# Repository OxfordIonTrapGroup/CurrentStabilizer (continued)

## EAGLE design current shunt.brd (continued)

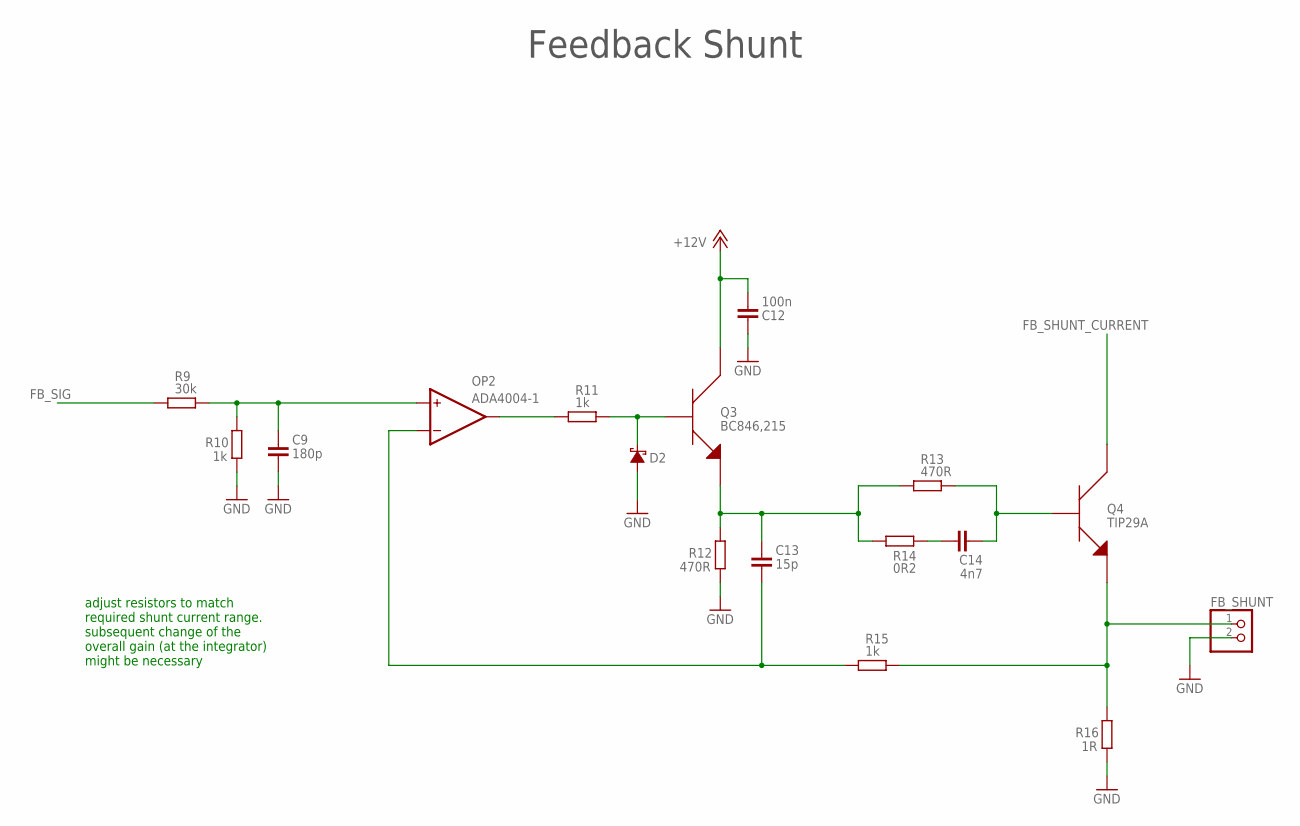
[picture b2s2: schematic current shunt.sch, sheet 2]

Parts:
C9: 180p; 0603
C12: 100n; 0603
C13: 15p; 0603
C14: 4n7; 0603
D2: DIODE_SCHOTTKY; SOD123F
FB_SHUNT: PINHD-1X2; 1X02
OP2: ADA4004-1; SOT23-5
Q3: BC846,215; SOT23
Q4: TIP29A; TO-220_DETATCHED
R9: 30k; 0603
R10, R11, R15: 1k; 0603
R12, R13: 470R; 0603
R14: 0R2; 0603
R16: 1R; 0603

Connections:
+12V: C12.1, Q3.3 (COLLECTOR); also elsewhere on the board
FB_SHUNT_CURRENT: Q4.COLLECTOR; also elsewhere on the board
FB_SIG: R9.1; also elsewhere on the board
FF_SHUNT: FB_SHUNT.1, Q4.EMITTER, R15.2, R16.2
GND: C9.2, C12.2, D2.P$2 (A), FB_SHUNT.2, R10.1, R12.1, R16.1; also elsewhere on the board
unnamed: C13.2, OP2.4 (-IN), R15.1
unnamed: C9.1, OP2.3 (+IN), R9.2, R10.2
unnamed: OP2.1 (OUT), R11.1
unnamed: D2.P$1 (K), Q3.1 (BASE), R11.2
unnamed: C13.1, Q3.2 (EMITTER), R12.2, R13.1, R14.1
unnamed: C14.2, Q4.BASE, R13.2
unnamed: C14.1, R14.2

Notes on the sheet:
Feedback Shunt
adjust resistors to match required shunt current range. subsequent change of the overall gain (at the integrator) might be necessary

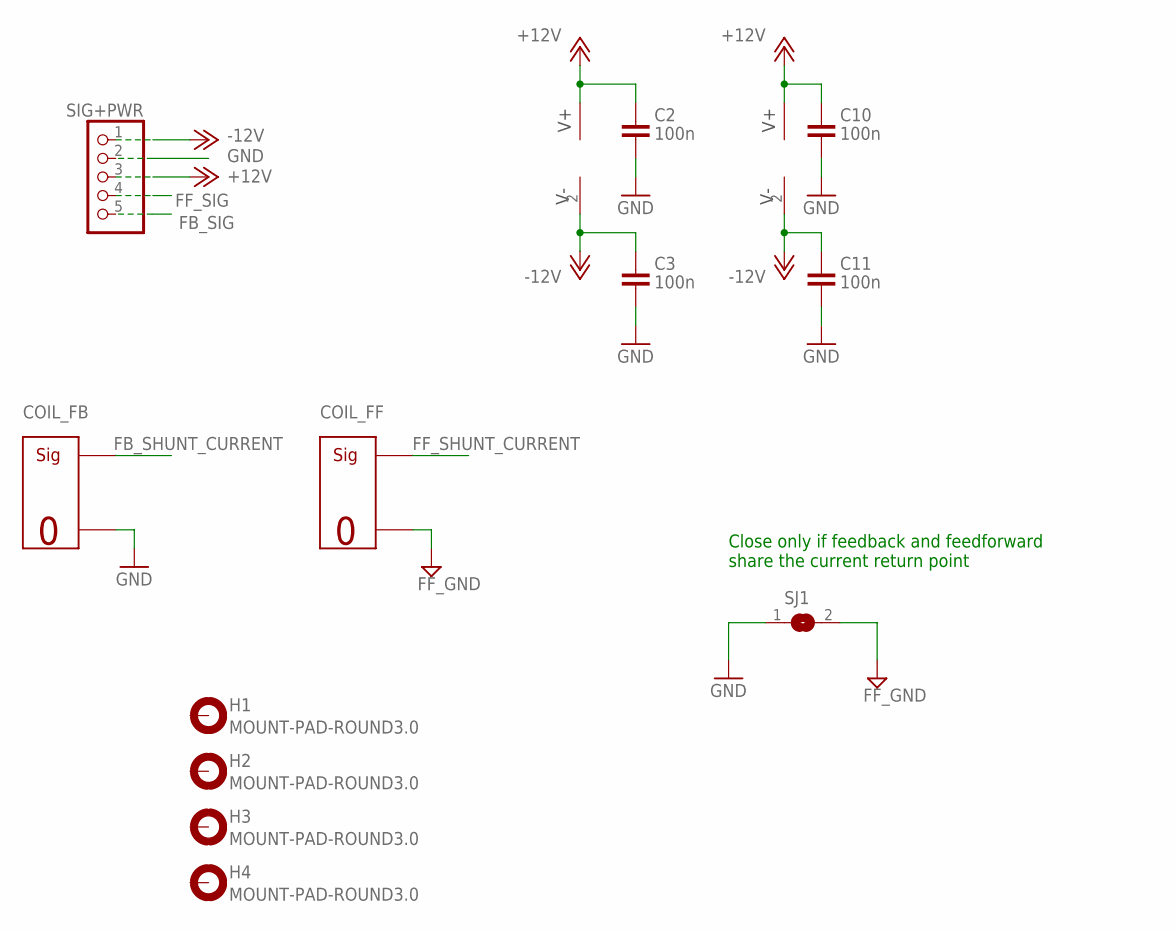
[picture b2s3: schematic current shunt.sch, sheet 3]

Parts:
C2, C3, C10, C11: 100n; 0603
COIL_FB: MOLEX_SIG_2PIN; MOLEX-2PIN
COIL_FF: MOLEX_SIG_2PIN; MOLEX-2PIN
H1, H2, H3, H4: MOUNT-PAD-ROUND3.0; 3,0-PAD
OP1, OP2: ADA4004-1; SOT23-5
SIG+PWR: MOLEX-KK-1X5; MOLEX-KK-5PIN
SJ1: SJ

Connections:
+12V: C2.1, C10.1, OP1.5 (V+), OP2.5 (V+), SIG+PWR.3; also elsewhere on the board
-12V: C3.1, C11.1, OP1.2 (V-), OP2.2 (V-), SIG+PWR.1
FB_SHUNT_CURRENT: COIL_FB.2 (SIG); also elsewhere on the board
FB_SIG: SIG+PWR.5; also elsewhere on the board
FF_GND: COIL_FF.1 (GND), SJ1.2; also elsewhere on the board
FF_SHUNT_CURRENT: COIL_FF.2 (SIG); also elsewhere on the board
FF_SIG: SIG+PWR.4; also elsewhere on the board
GND: C2.2, C3.2, C10.2, C11.2, COIL_FB.1 (GND), SIG+PWR.2, SJ1.1; also elsewhere on the board

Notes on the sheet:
Close only if feedback and feedforward share the current return point

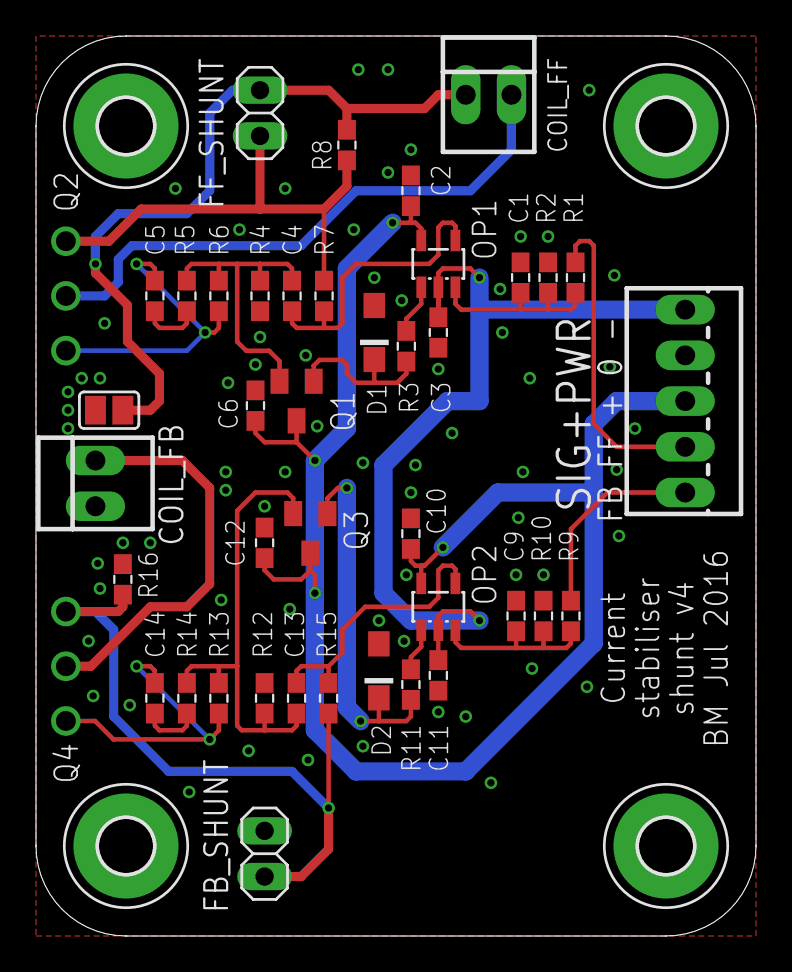
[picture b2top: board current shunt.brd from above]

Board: 2 copper layers, 40.0 x 50.0 mm, 46 parts (0 on the bottom side), 24 nets.

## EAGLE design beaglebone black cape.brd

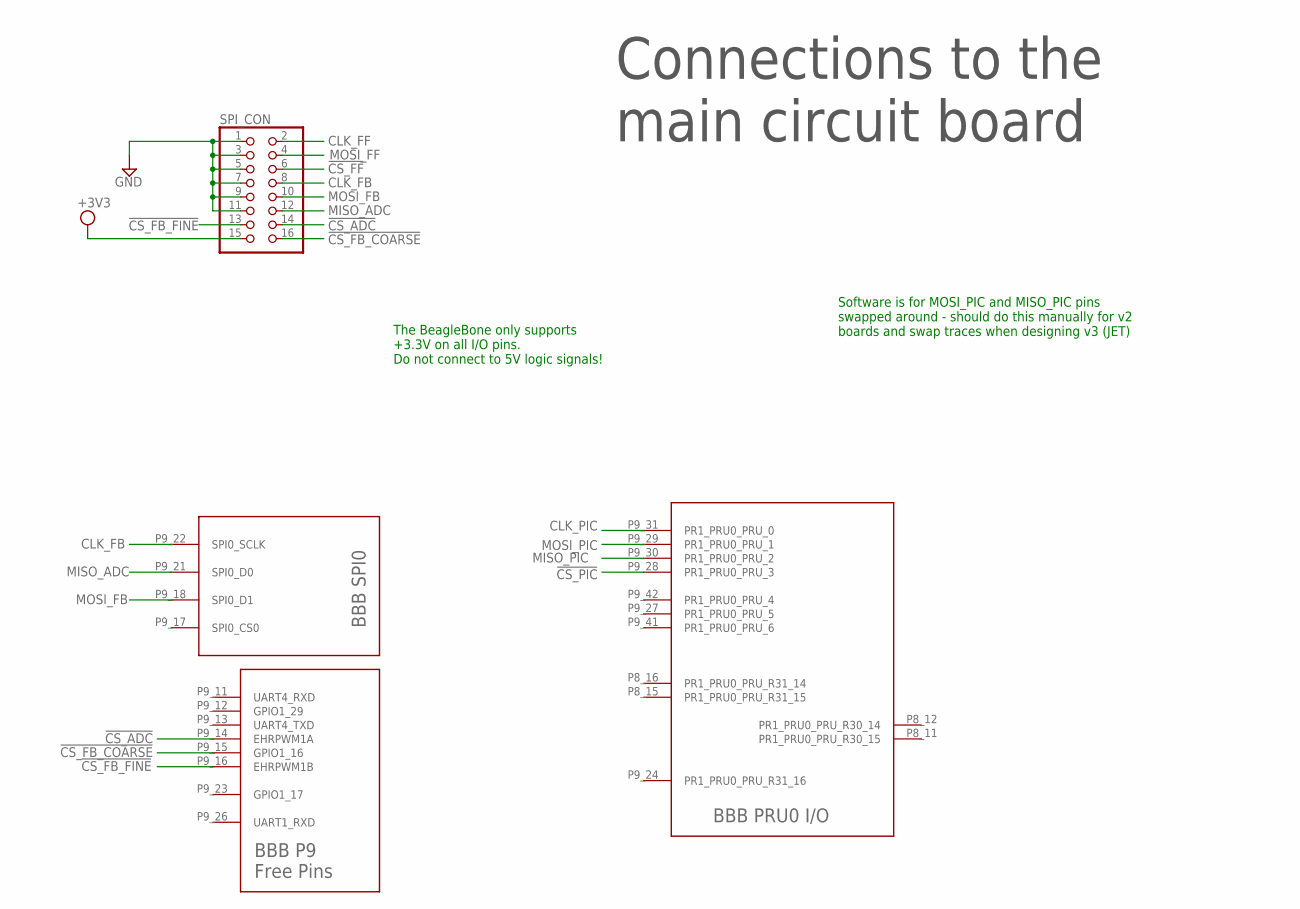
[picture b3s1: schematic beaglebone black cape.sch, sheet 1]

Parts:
SPI_CON: HEADER-2X8; HEADER-2X8-BOX
U$1: BEAGLEBONE_BLACK

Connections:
3V3: SPI_CON.15; also elsewhere on the board
!CS_ADC: SPI_CON.14, U$1.P9_14 (EHRPWM1A)
!CS_FB_COARSE: SPI_CON.16, U$1.P9_15 (GPIO1_16)
!CS_FB_FINE: SPI_CON.13, U$1.P9_16 (EHRPWM1B)
!CS_FF: SPI_CON.6; also elsewhere on the board
!CS_PIC: U$1.P9_28 (PR1_PRU0_PRU_3)
AGND: U$1.P9_34 (AGND)
CLK_FB: SPI_CON.8, U$1.P9_22 (SPI0_SCLK)
CLK_FF: SPI_CON.2; also elsewhere on the board
CLK_PIC: U$1.P9_31 (PR1_PRU0_PRU_0); also elsewhere on the board
GND: SPI_CON.1, SPI_CON.3, SPI_CON.5, SPI_CON.7, SPI_CON.9, SPI_CON.11; also elsewhere on the board
MISO_ADC: SPI_CON.12, U$1.P9_21 (SPI0_D0)
MISO_PIC: U$1.P9_30 (PR1_PRU0_PRU_2); also elsewhere on the board
MOSI_FB: SPI_CON.10, U$1.P9_18 (SPI0_D1)
MOSI_FF: SPI_CON.4; also elsewhere on the board
MOSI_PIC: U$1.P9_29 (PR1_PRU0_PRU_1); also elsewhere on the board
PWR_BUT: U$1.P9_9 (PWR_BUT)
SYS_5V: U$1.P9_7 (SYS_5V), U$1.P9_8 (SYS_5V)
SYS_RESETN: U$1.P9_10 (SYS_RESETN)
VADC: U$1.P9_32 (VADC)

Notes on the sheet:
The BeagleBone only supports +3.3V on all I/O pins. Do not connect to 5V logic signals!
Connections to the main circuit board
Software is for MOSI_PIC and MISO_PIC pins swapped around - should do this manually for v2 boards and swap traces when designing v3 (JET)

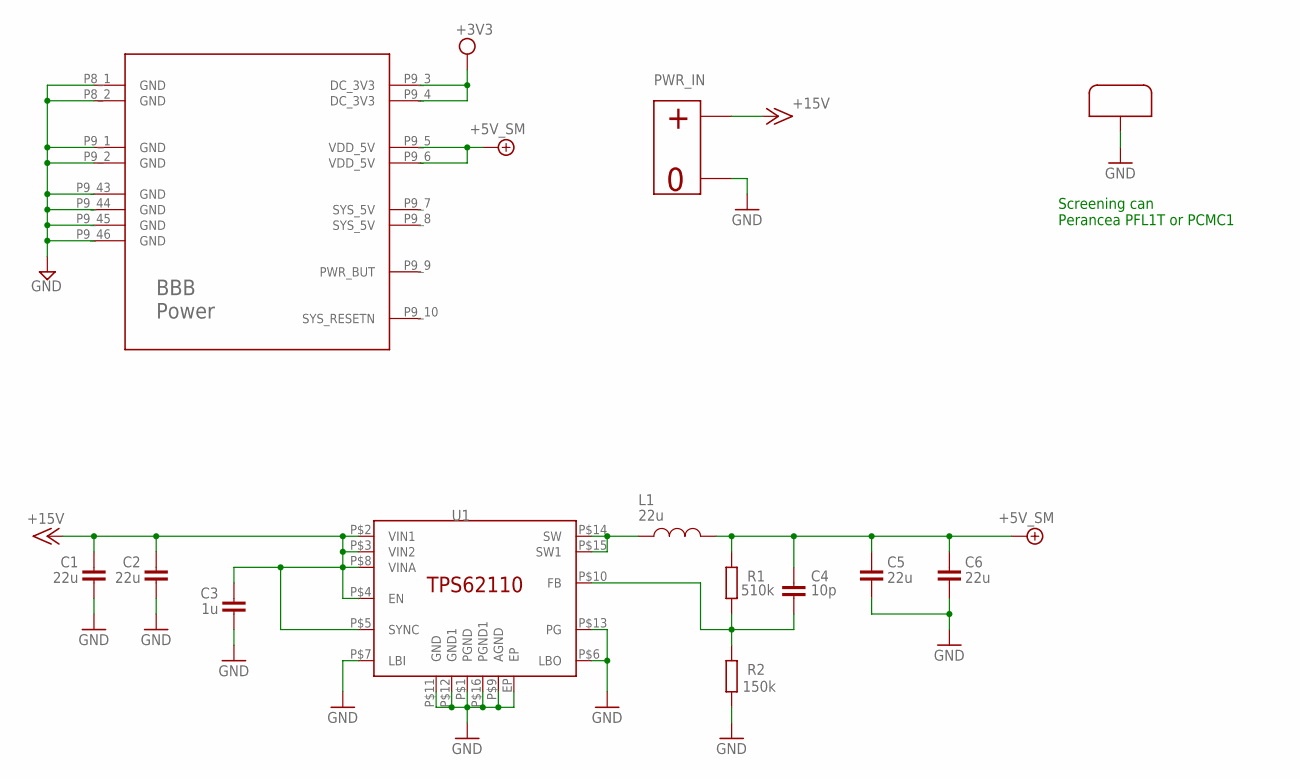
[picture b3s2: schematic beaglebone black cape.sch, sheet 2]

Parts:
C1, C2, C5, C6: 22u; 0805
C3: 1u; 0805
C4: 10p; 0603
L1: 22u; XAL6060
PWR_IN: MOLEX_POWER_2PIN; MOLEX-2PIN
R1: 510k; 0603
R2: 150k; 0603
U1: TPS62110; QFN16_4
U$1: BEAGLEBONE_BLACK
U$2: SCREENING_CAN; SCREENING_CAN_20X20

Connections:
3V3: U$1.P9_3 (DC_3V3), U$1.P9_4 (DC_3V3); also elsewhere on the board
+5VSM: C4.1, C5.1, C6.1, L1.P$2 (P2), R1.2, U$1.P9_5 (VDD_5V), U$1.P9_6 (VDD_5V)
+15V: C1.1, C2.1, C3.1, PWR_IN.2 (+), U1.P$2 (VIN1), U1.P$3 (VIN2), U1.P$4 (EN), U1.P$5 (SYNC), U1.P$8 (VINA)
AGND: U$1.P9_34 (AGND)
GND: C1.2, C2.2, C3.2, C5.2, C6.2, PWR_IN.1 (GND), R2.1, U1.EP, U1.P$1 (PGND), U1.P$6 (LBO), U1.P$7 (LBI), U1.P$9 (AGND), U1.P$11 (GND), U1.P$12 (GND1), U1.P$13 (PG), U1.P$16 (PGND1), U$1.P8_1 (GND), U$1.P8_2 (GND), U$1.P9_1 (GND), U$1.P9_2 (GND), U$1.P9_43 (GND), U$1.P9_44 (GND), U$1.P9_45 (GND), U$1.P9_46 (GND), U$2.1, U$2.2, U$2.3, U$2.4; also elsewhere on the board
unnamed: L1.P$1 (P1), U1.P$14 (SW), U1.P$15 (SW1)
unnamed: C4.2, R1.1, R2.2, U1.P$10 (FB)
PWR_BUT: U$1.P9_9 (PWR_BUT)
SYS_5V: U$1.P9_7 (SYS_5V), U$1.P9_8 (SYS_5V)
SYS_RESETN: U$1.P9_10 (SYS_RESETN)
VADC: U$1.P9_32 (VADC)

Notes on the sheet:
Screening can Perancea PFL1T or PCMC1

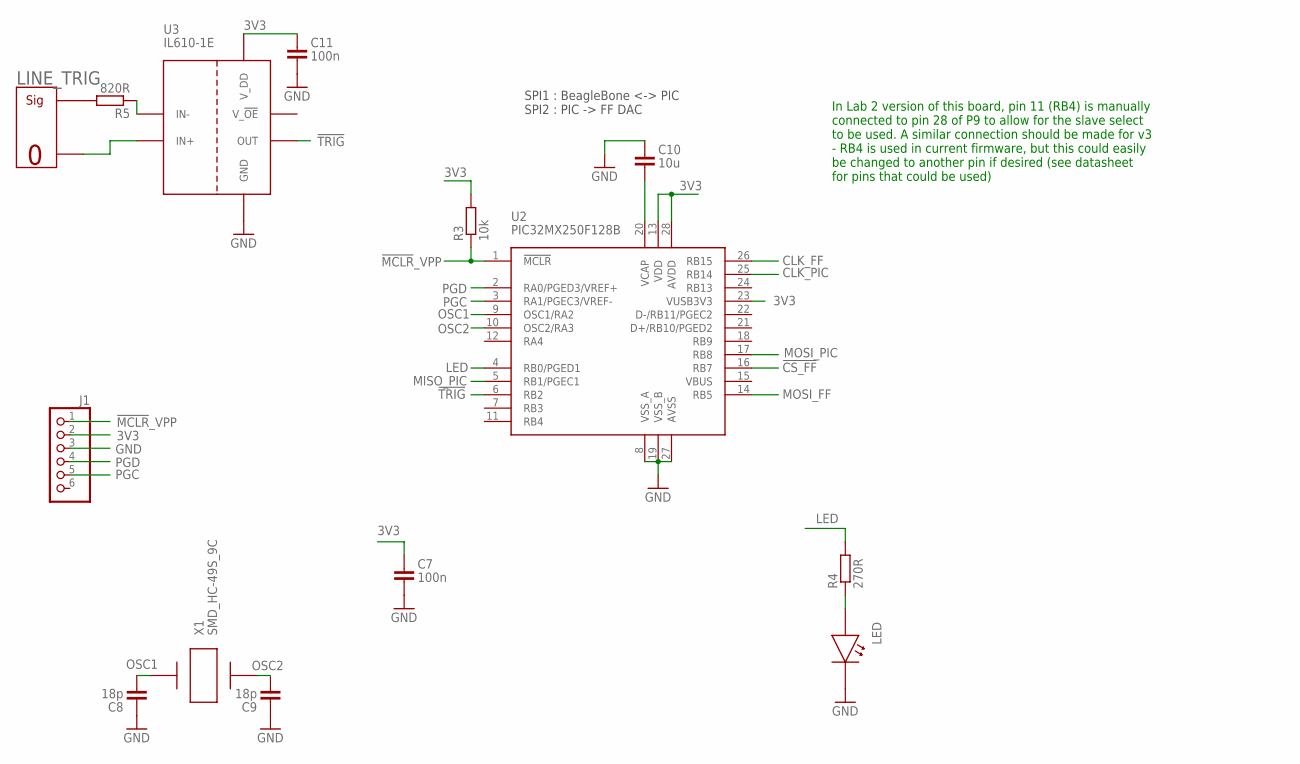
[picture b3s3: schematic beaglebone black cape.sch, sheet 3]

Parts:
C7, C11: 100n; 0603
C8, C9: 18p; 0603
C10: 10u; 0805
J1: HEADER-1X6; 1X06
LED: OSRAMLED; 0805DIODE
LINE_TRIG: MOLEX_SIG_2PIN; MOLEX-2PIN
R3: 10k; 0603
R4: 270R; 0603
R5: 820R; 0603
U2: PIC32MX250F128B; SSOP28
U3: IL610-1E; MSOP8
X1: SMD_HC-49S_9C

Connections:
3V3: C7.1, C11.1, J1.2, R3.2, U2.13 (VDD), U2.23 (VUSB3V3), U2.28 (AVDD), U3.8 (V_DD); also elsewhere on the board
!CS_FF: U2.16 (RB7); also elsewhere on the board
!MCLR!_VPP: J1.1, R3.1, U2.1 (!MCLR)
!TRIG: U2.6 (RB2), U3.6 (OUT)
CLK_FF: U2.26 (RB15); also elsewhere on the board
CLK_PIC: U2.25 (RB14); also elsewhere on the board
GND: C7.2, C8.1, C9.1, C10.1, C11.2, J1.3, LED.2, LINE_TRIG.1 (GND), U2.8 (VSS_A), U2.19 (VSS_B), U2.27 (AVSS), U3.2 (IN+), U3.5 (GND); also elsewhere on the board
LED: R4.2, U2.4 (RB0/PGED1)
MISO_PIC: U2.5 (RB1/PGEC1); also elsewhere on the board
MOSI_FF: U2.14 (RB5); also elsewhere on the board
MOSI_PIC: U2.17 (RB8); also elsewhere on the board
unnamed: LED.1, R4.1
unnamed: R5.1, U3.3 (IN-)
unnamed: LINE_TRIG.2 (SIG), R5.2
OSC1: C8.2, U2.9 (OSC1/RA2), X1.P$2
OSC2: C9.2, U2.10 (OSC2/RA3), X1.P$1
PGC: J1.5, U2.3 (RA1/PGEC3/VREF-)
PGD: J1.4, U2.2 (RA0/PGED3/VREF+)
VCAP: C10.2, U2.20 (VCAP)

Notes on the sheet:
SPI1 : BeagleBone <-> PIC SPI2 : PIC -> FF DAC
In Lab 2 version of this board, pin 11 (RB4) is manually connected to pin 28 of P9 to allow for the slave select to be used. A similar connection should be made for v3 - RB4 is used in current firmware, but this could easily be changed to another pin if desired (see datasheet for pins that could be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

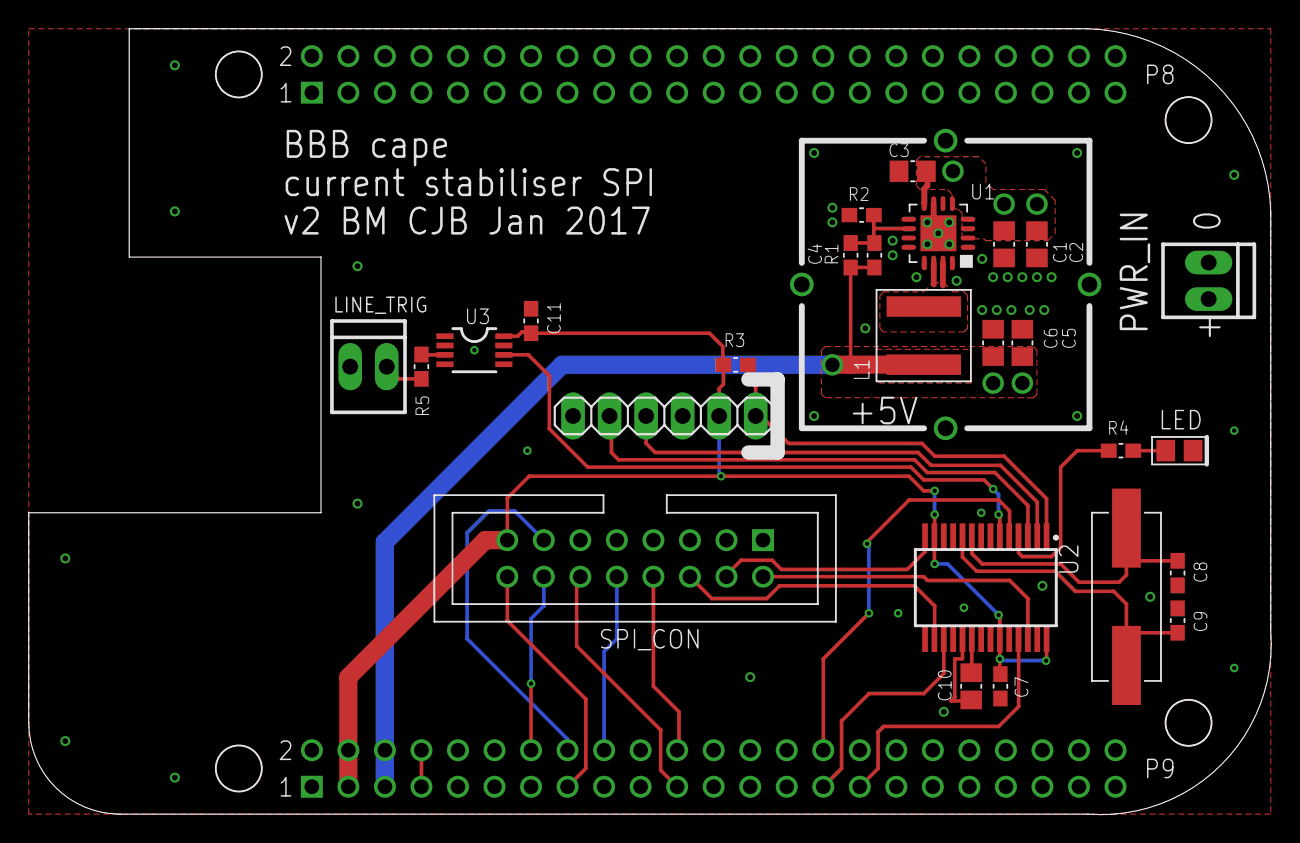
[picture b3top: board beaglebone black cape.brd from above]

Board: 2 copper layers, 86.3 x 54.5 mm, 28 parts (0 on the bottom side), 30 nets.

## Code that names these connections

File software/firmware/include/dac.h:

#pragma once

#include <stdint.h>

void dac_init(void);

void dac_setCoarse(uint16_t val);
void dac_setFine(uint16_t val);
void dac_setFeedForward(uint16_t val);


#define SDO_FB  (LATBbits.LATB1)
#define SCK_FB  (LATBbits.LATB3)
#define CS_FB_FINE  (LATBbits.LATB4)
#define CS_FB_COARSE    (LATAbits.LATA4)
#define CS_FF   (LATBbits.LATB7)

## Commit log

2018-09-12 add .gitignore
2018-09-12 add beaglebone cape
2018-09-12 .gitignore: ignore epf files
2018-09-12 add main board
2018-09-12 add bom
2018-09-12 add current shunt
2018-09-12 remove old bom
2019-03-15 add python notebook with analysis of noise and long-term stability
2019-03-22 add firmware
